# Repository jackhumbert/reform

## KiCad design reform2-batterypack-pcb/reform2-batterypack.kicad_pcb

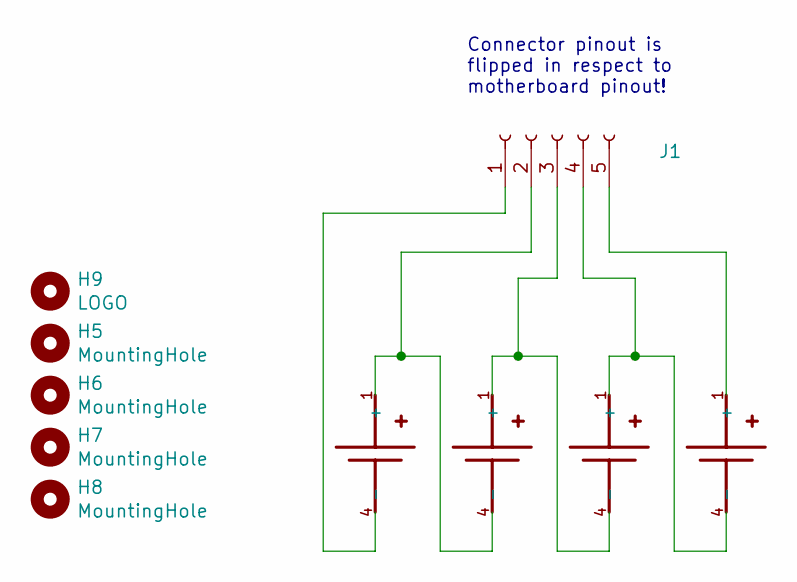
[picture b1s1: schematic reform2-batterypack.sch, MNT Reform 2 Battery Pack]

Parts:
H5, H6, H7, H8: MountingHole; MountingHole_2.2mm_M2
H9: LOGO; mnt-minilogo
J1: Conn_01x05_Female; Molex_Pico-Lock_504050-0591_1x05-1MP_P1.50mm_Horizontal
U1, U2, U3, U4: KEYSTONE_54; Keystone54

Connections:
unnamed: J1.1, U1.4 (-), U1.5 (-), U1.6 (-)
unnamed: J1.2, U1.1 (+), U1.2 (+), U1.3 (+), U2.4 (-), U2.5 (-), U2.6 (-)
unnamed: J1.3, U2.1 (+), U2.2 (+), U2.3 (+), U3.4 (-), U3.5 (-), U3.6 (-)
unnamed: J1.4, U3.1 (+), U3.2 (+), U3.3 (+), U4.4 (-), U4.5 (-), U4.6 (-)
unnamed: J1.5, U4.1 (+), U4.2 (+), U4.3 (+)

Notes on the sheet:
Connector pinout is flipped in respect to motherboard pinout!

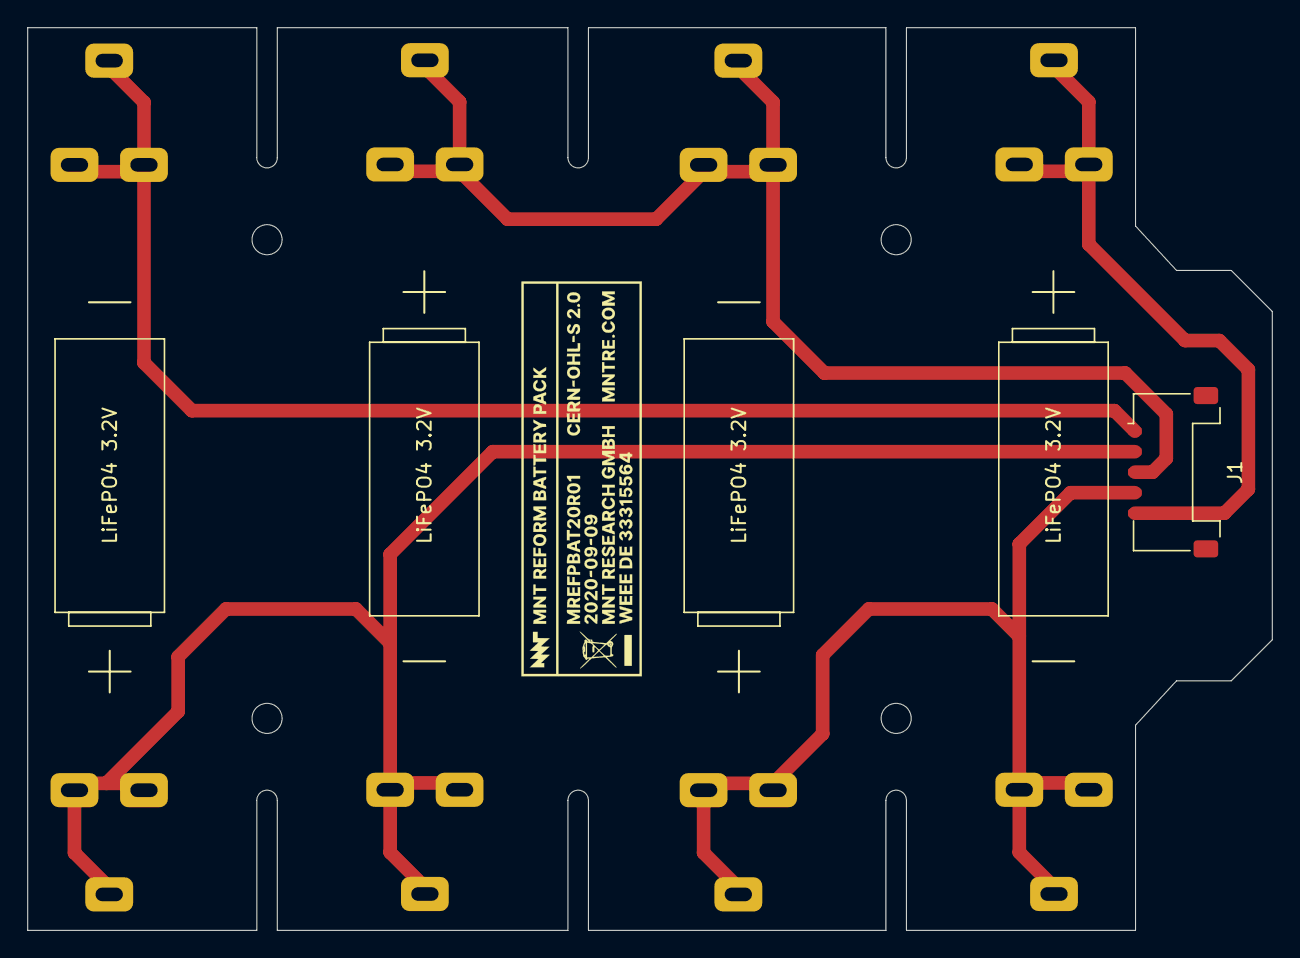
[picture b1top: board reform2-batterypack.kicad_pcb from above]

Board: 2 copper layers, 91.0 x 66.0 mm, 9 parts (0 on the bottom side), 5 nets.

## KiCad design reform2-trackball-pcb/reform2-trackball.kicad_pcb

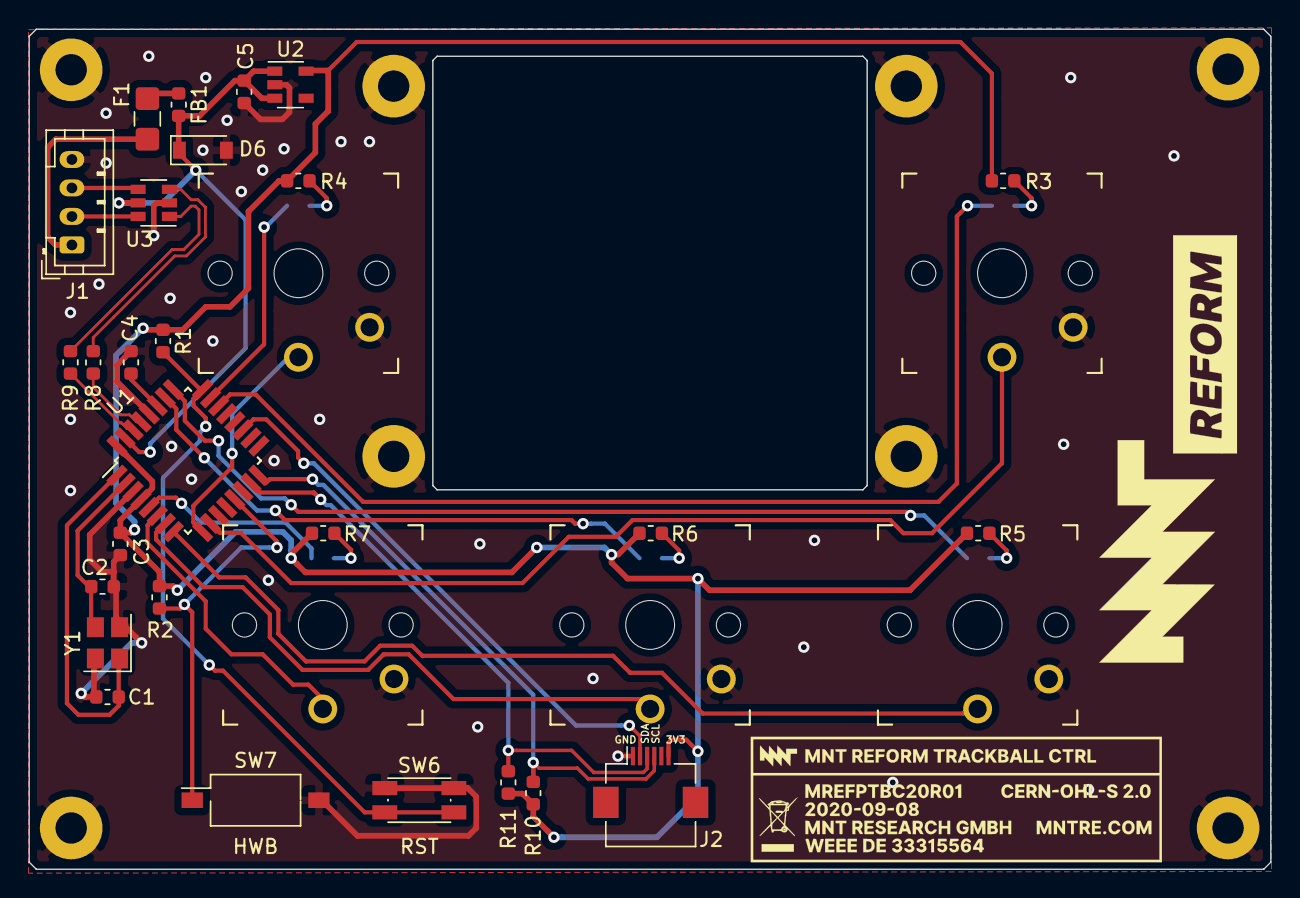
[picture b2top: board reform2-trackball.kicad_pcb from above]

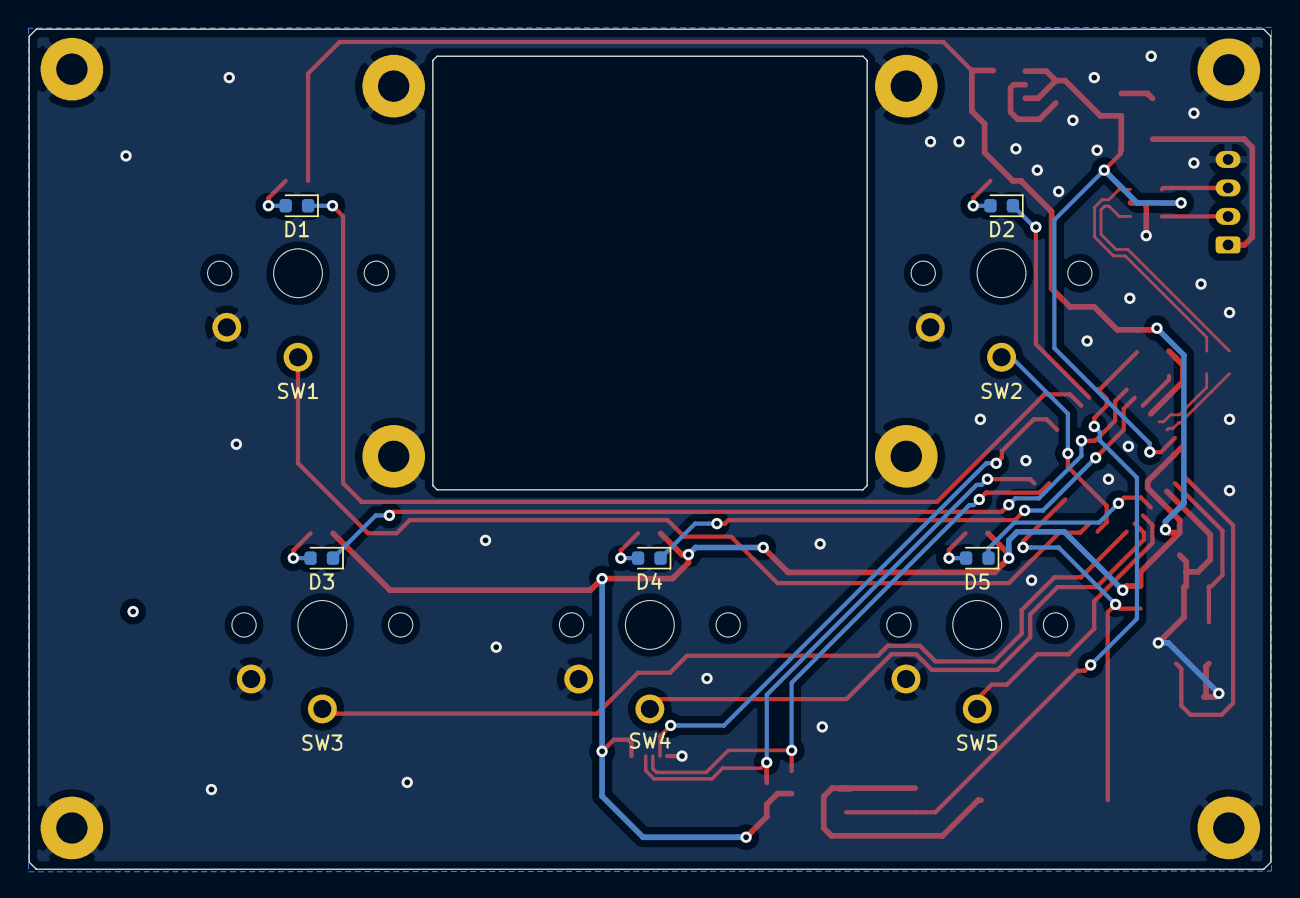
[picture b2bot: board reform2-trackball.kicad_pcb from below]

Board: 2 copper layers, 87.2 x 59.0 mm, 47 parts (10 on the bottom side), 34 nets.

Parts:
C1, C2: 18pF; C_0603_1608Metric
C3, C5: 0.1uF; C_0603_1608Metric
C4: 1uF; C_0603_1608Metric
D1, D2, D3, D4, D5: LED_Small; LED_0603_1608Metric
D6: BZT52-B5V6J; D_SOD-123
F1: 0ZCJ0075AF2E; Fuse_1206_3216Metric_Castellated
FB1: BLM18PG221SH1D; L_0603_1608Metric
J1: Conn_USB; JST_PH_B4B-PH-K_1x04_P2.00mm_Vertical
J2: Conn_01x06_Female; Hirose_FH12-6S-0.5SH_1x06-1MP_P0.50mm_Horizontal
MK1: BADGE; mntreform-trackball-badge
MK5, MK6, MK7, MK8, MK9, MK10, MK11, MK12: Mounting_Hole; MountingHole_2.2mm_M2_Pad
MK13: LOGO; mntreform
R1, R2: 10k; R_0603_1608Metric
R3, R4, R5, R6, R7: 475; R_0603_1608Metric
R8, R9: 22; R_0603_1608Metric
R10, R11: 4.7k; R_0603_1608Metric
SW1, SW2, SW3, SW4, SW5: Choc; PG1350
SW6: SW_RST; Diptronics-PTLP2
SW7: SW_HWB; SW_DIP_SPSTx01_Slide_Omron_A6S-110x_W8.9mm_P2.54mm
U1: ATmega32U2-AU; TQFP-32_7x7mm_Pitch0.8mm
U2: TLV75533PDBV; SOT-23-5
U3: USBLC6-2SC6; SOT-23-6
Y1: Crystal_GND24; Crystal_SMD_3225-4Pin_3.2x2.5mm

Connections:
+3V3: C3.1, J2.6, R1.1, R2.2, R3.2, R4.2, R5.2, R6.2, R7.2, R10.2, R11.2, U1.4, U1.32, U2.5
+5V: C5.1, D6.1, FB1.2, U1.31, U2.1, U2.3, U3.5
/5V_IN: F1.2, J1.1
/D+: R8.2, U1.29
/D-: R9.1, U1.30
/PD+: J1.3, U3.4
/PD-: J1.2, U3.6
/UD+: R8.1, U3.3
/UD-: R9.2, U3.1
GND: C1.2, C2.1, C3.2, C4.2, C5.2, D6.2, J1.4, J2.1, MK5.1, MK6.1, MK7.1, MK8.1, MK9.1, MK10.1, MK11.1, MK12.1, SW1.2, SW2.2, SW3.2, SW4.2, SW5.2, SW6.1, SW7.2, U1.3, U1.28, U2.2, U3.2, Y1.2, Y1.4
MT: J2.2, U1.19
unnamed: C1.1, U1.1, Y1.1
unnamed: C2.2, U1.2, Y1.3
unnamed: C4.1, U1.27
unnamed: D1.1, U1.22
unnamed: D1.2, R3.1
unnamed: D2.1, U1.23
unnamed: D2.2, R4.1
unnamed: D3.1, U1.25
unnamed: D3.2, R5.1
unnamed: D4.1, U1.26
unnamed: D4.2, R6.1
unnamed: D5.1, U1.5
unnamed: D5.2, R7.1
unnamed: F1.1, FB1.1
unnamed: R1.2, SW6.2, U1.24
unnamed: R2.1, SW7.1, U1.13
unnamed: SW1.1, U1.10
unnamed: SW2.1, U1.9
unnamed: SW3.1, U1.8
unnamed: SW4.1, U1.7
unnamed: SW5.1, U1.6
SCL: J2.4, R10.1, U1.16
SDA: J2.3, R11.1, U1.15

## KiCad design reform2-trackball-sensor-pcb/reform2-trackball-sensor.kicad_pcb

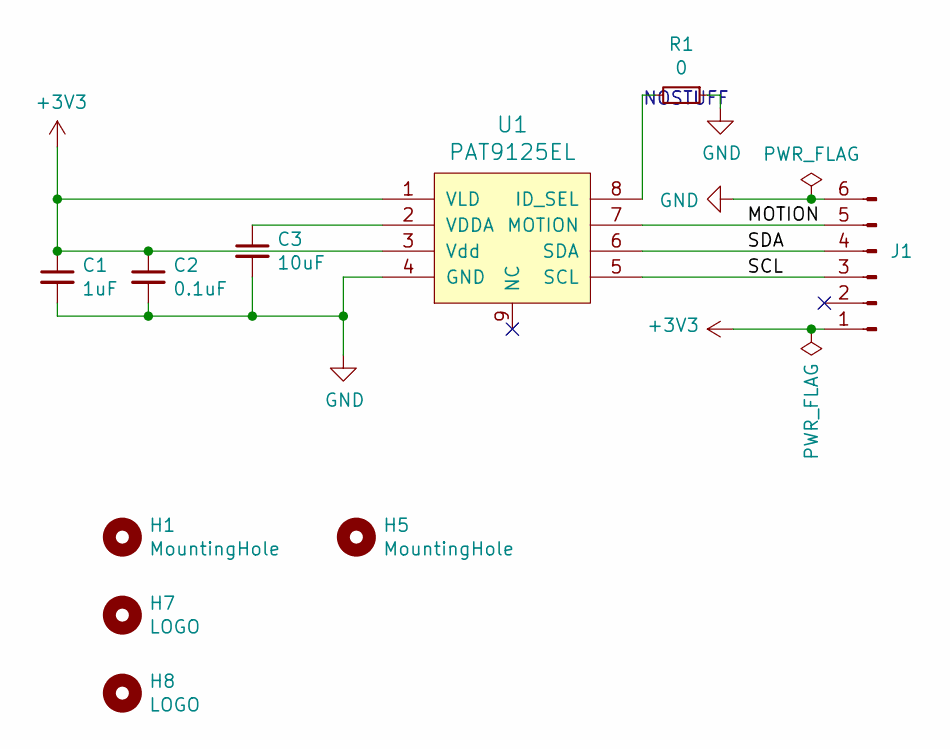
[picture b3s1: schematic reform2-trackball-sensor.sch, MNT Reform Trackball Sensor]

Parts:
C1: 1uF; C_0603_1608Metric
C2: 0.1uF; C_0603_1608Metric
C3: 10uF; C_0603_1608Metric
H1, H5: MountingHole; MountingHole_2.2mm_M2
H7: LOGO; mnt-minilogo
H8: LOGO; reform2-trackball-sensor-badge
J1: Conn_01x06_Male; Hirose_FH12-6S-0.5SH_1x06-1MP_P0.50mm_Horizontal
R1: 0; R_0603_1608Metric
U1: PAT9125EL

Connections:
+3V3: C1.1, C2.1, J1.1, U1.1 (VLD), U1.3 (Vdd)
/MOTION: J1.5, U1.7 (MOTION)
/SCL: J1.3, U1.5 (SCL)
/SDA: J1.4, U1.6 (SDA)
GND: C1.2, C2.2, C3.2, J1.6, R1.1, U1.4 (GND)
unnamed: C3.1, U1.2 (VDDA)
unnamed: R1.2, U1.8 (ID_SEL)

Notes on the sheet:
NOSTUFF

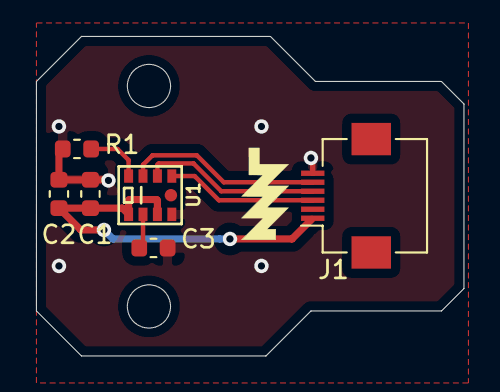
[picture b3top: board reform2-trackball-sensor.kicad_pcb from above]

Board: 2 copper layers, 23.8 x 17.8 mm, 10 parts (1 on the bottom side), 7 nets.

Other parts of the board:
H2: MountingHole; MountingHole_2.2mm_M2

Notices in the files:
reform2-batterypack-pcb/reform2-batterypack.sch:
License: CERN-OHL-S 2.0
